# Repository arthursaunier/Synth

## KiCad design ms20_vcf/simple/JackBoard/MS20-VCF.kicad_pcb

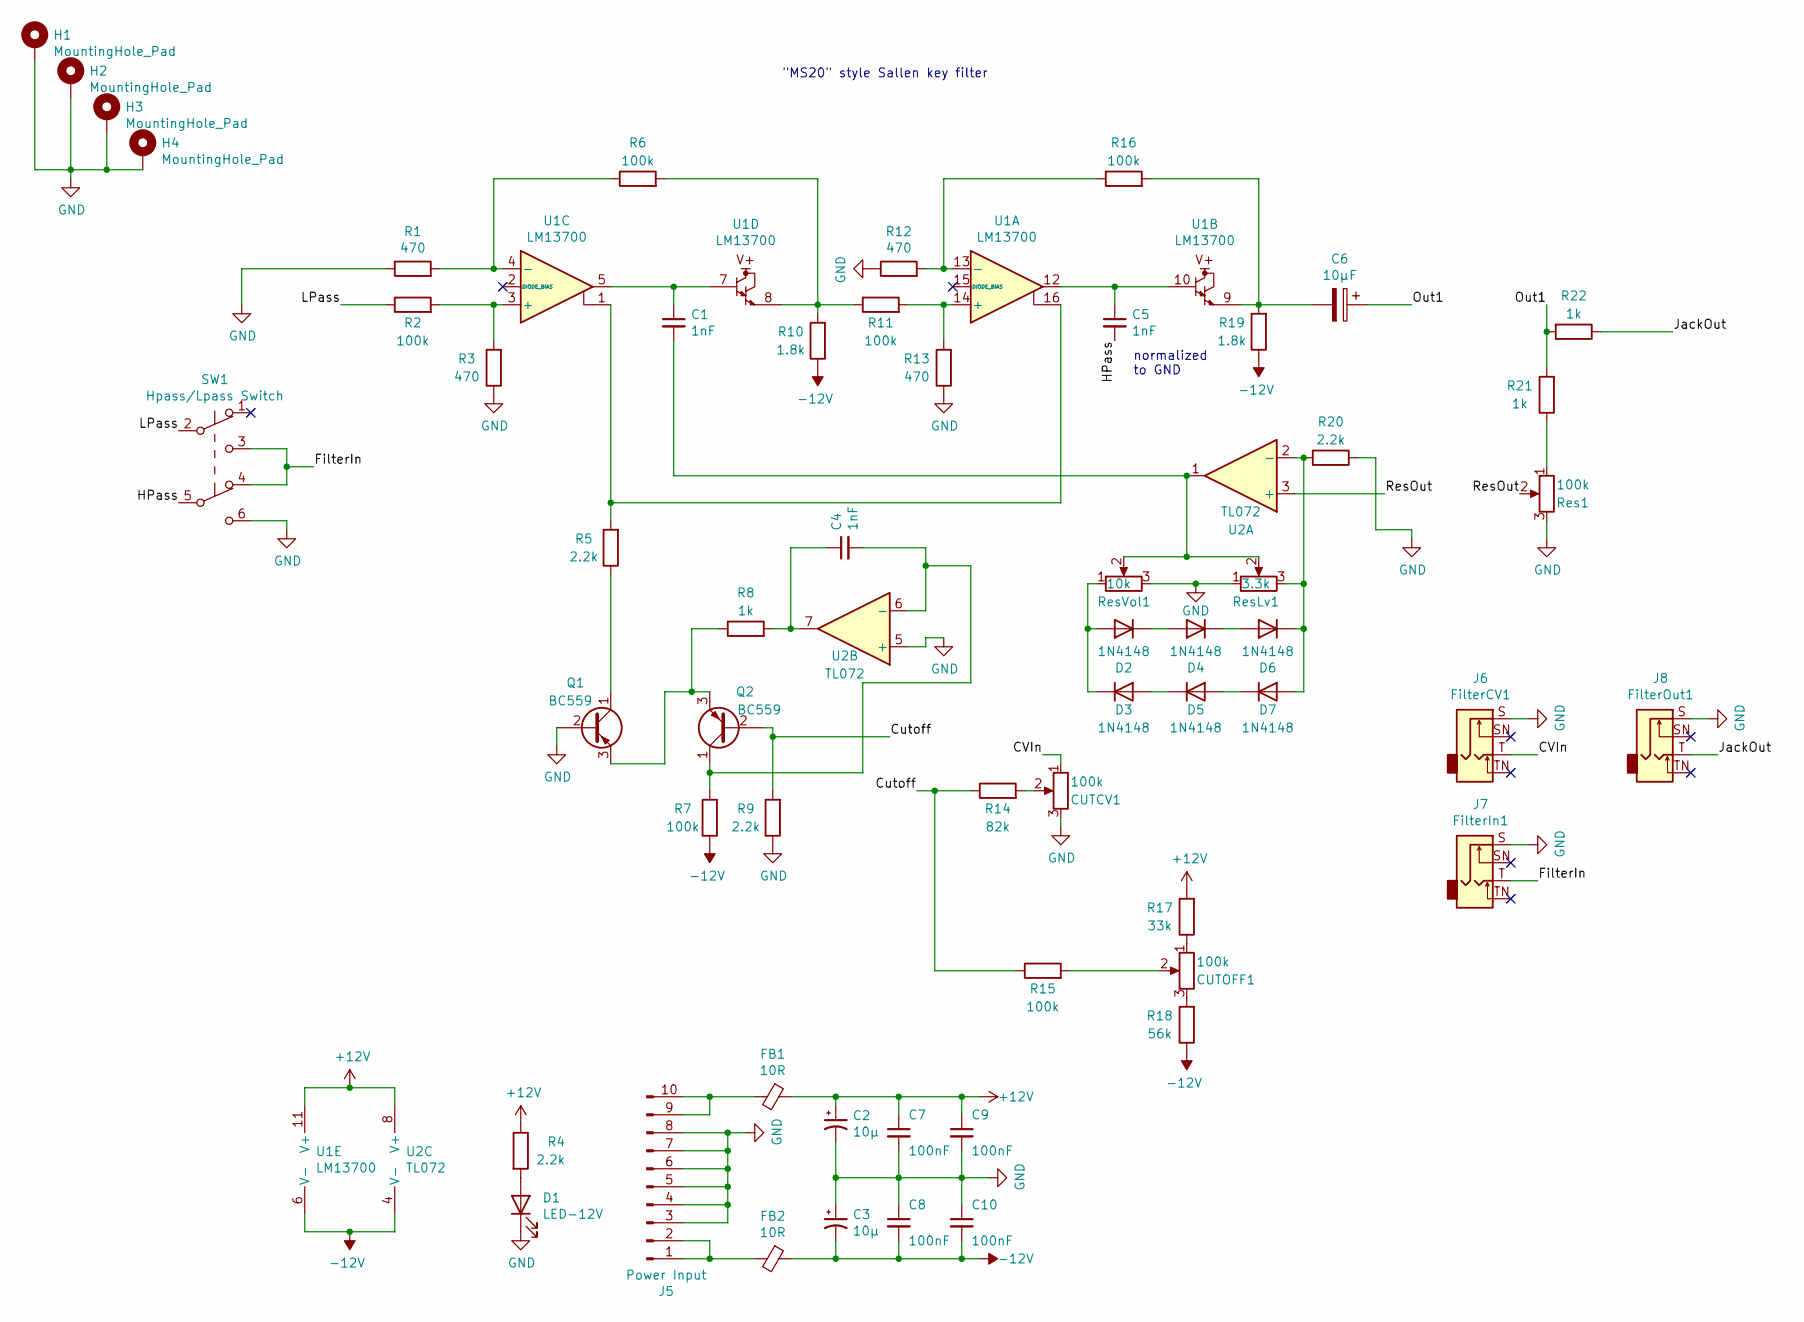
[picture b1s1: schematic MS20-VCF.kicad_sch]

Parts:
C1, C4, C5: 1nF; C_Disc_D7.0mm_W2.5mm_P5.00mm
C2, C3: 10µ; CP_Radial_D5.0mm_P2.00mm
C6: 10µF; CP_Radial_D5.0mm_P2.00mm
C7, C8, C9, C10: 100nF; C_Disc_D7.0mm_W2.5mm_P5.00mm
CUTCV1: 100k; Pot-bourns-alpha
CUTOFF1: 100k; Pot-bourns-alpha
D1: LED-12V; LED_D4.0mm
D2, D3, D4, D5, D6, D7: 1N4148; D_DO-35_SOD27_P7.62mm_Horizontal
FB1, FB2: 10R; L_Axial_L9.5mm_D4.0mm_P12.70mm_Horizontal_Fastron_SMCC
H1, H2, H3, H4: MountingHole_Pad; Doepfer Mounting hole
J5: Power Input; IDC-Header_2x05_P2.54mm_Vertical
J6: FilterCV1; Thonkiconn
J7: FilterIn1; Thonkiconn
J8: FilterOut1; Thonkiconn
Q1, Q2: BC559; TO-92_Inline_Wide
R1, R3, R12, R13: 470; R_Axial_DIN0207_L6.3mm_D2.5mm_P10.16mm_Horizontal
R2, R6, R7, R11, R15, R16: 100k; R_Axial_DIN0207_L6.3mm_D2.5mm_P10.16mm_Horizontal
R4, R5, R9, R20: 2.2k; R_Axial_DIN0207_L6.3mm_D2.5mm_P10.16mm_Horizontal
R8, R21, R22: 1k; R_Axial_DIN0207_L6.3mm_D2.5mm_P10.16mm_Horizontal
R10, R19: 1.8k; R_Axial_DIN0207_L6.3mm_D2.5mm_P10.16mm_Horizontal
R14: 82k; R_Axial_DIN0207_L6.3mm_D2.5mm_P10.16mm_Horizontal
R17: 33k; R_Axial_DIN0207_L6.3mm_D2.5mm_P10.16mm_Horizontal
R18: 56k; R_Axial_DIN0207_L6.3mm_D2.5mm_P10.16mm_Horizontal
Res1: 100k; Pot-bourns-alpha
ResLv1: 3.3k; Potentiometer_Bourns_3386C_Horizontal
ResVol1: 10k; Potentiometer_Bourns_3386C_Horizontal
SW1: Hpass/Lpass Switch; SW_DPDT_Toggle
U1: LM13700; SOIC-16_3.9x9.9mm_P1.27mm
U2: TL072; DIP-8_W7.62mm_Socket

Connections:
+12V: C2.1, C7.1, C9.1, FB1.1, R4.1, R17.2, U1.11 (V+), U2.8 (V+)
-12V: C3.2, C8.2, C10.2, FB2.1, R7.1, R10.1, R18.1, R19.1, U1.6 (V-), U2.4 (V-)
/CVIn: CUTCV1.1, J6.T
/Cutoff: Q2.2 (B), R9.2, R14.1, R15.1
/FilterIn: J7.T, SW1.3 (C), SW1.4 (A)
/HPass: C5.2, SW1.5 (B)
/JackOut: J8.T, R22.1
/LPass: R2.1, SW1.2 (B)
/Out1: C6.1, R21.2, R22.2
/ResOut: Res1.2, U2.3 (+)
GND: C2.2, C3.1, C7.2, C8.1, C9.2, C10.1, CUTCV1.3, D1.1 (K), H1.1, H2.1, H3.1, H4.1, J5.3, J5.4, J5.5, J5.6, J5.7, J5.8, J6.S, J7.S, J8.S, Q1.2 (B), R1.1, R3.1, R9.1, R12.1, R13.1, R20.1, Res1.3, ResLv1.1, ResVol1.3, SW1.6 (C), U2.5 (+)
unnamed: C1.1, U1.5, U1.7
unnamed: C1.2, ResLv1.2, ResVol1.2, U2.1
unnamed: C4.1, R8.2, U2.7
unnamed: C4.2, Q2.1 (C), R7.2, U2.6 (-)
unnamed: C5.1, U1.10, U1.12
unnamed: C6.2, R16.2, R19.2, U1.9
unnamed: CUTOFF1.1, R17.1
unnamed: D1.2 (A), R4.2
unnamed: D2.1 (K), D4.2 (A)
unnamed: D2.2 (A), D3.1 (K), ResVol1.1
unnamed: D3.2 (A), D5.1 (K)
unnamed: D4.1 (K), D6.2 (A)
unnamed: D5.2 (A), D7.1 (K)
unnamed: D6.1 (K), D7.2 (A), R20.2, ResLv1.3, U2.2 (-)
unnamed: FB1.2, J5.9, J5.10
unnamed: FB2.2, J5.1, J5.2
unnamed: Q1.1 (C), R5.1
unnamed: Q1.3 (E), Q2.3 (E), R8.1
unnamed: R1.2, R6.1, U1.4 (-)
unnamed: R2.2, R3.2, U1.3 (+)
unnamed: R5.2, U1.1, U1.16
unnamed: R6.2, R10.2, R11.1, U1.8
unnamed: R11.2, R13.2, U1.14 (+)
unnamed: R12.2, R16.1, U1.13 (-)
unnamed: CUTCV1.2, R14.2
unnamed: CUTOFF1.2, R15.2
unnamed: CUTOFF1.3, R18.2
unnamed: R21.1, Res1.1

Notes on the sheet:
normalized to GND
"MS20" style Sallen key filter

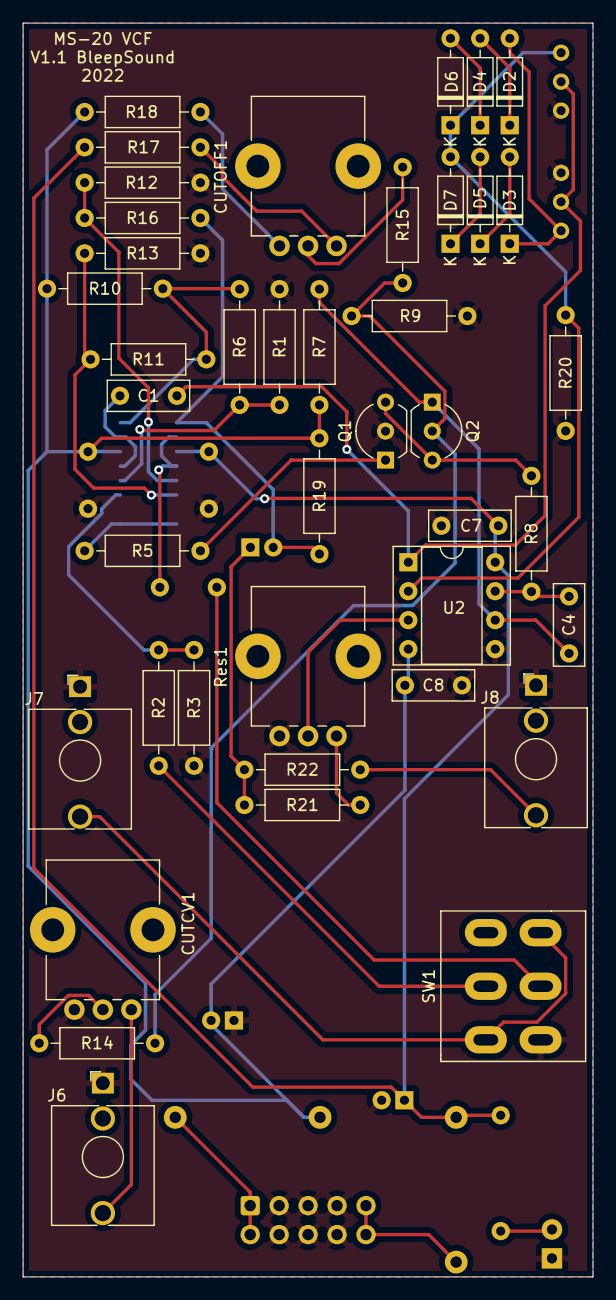
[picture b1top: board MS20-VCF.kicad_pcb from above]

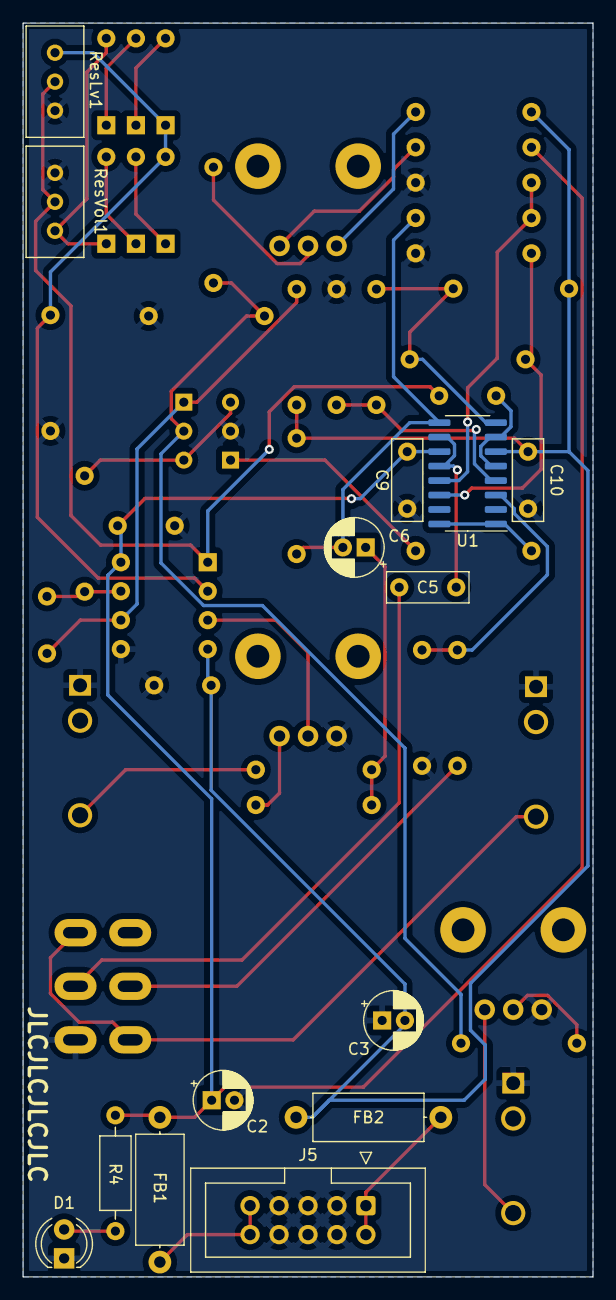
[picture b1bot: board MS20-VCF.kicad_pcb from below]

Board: 2 copper layers, 50.0 x 110.0 mm, 55 parts (14 on the bottom side), 39 nets.

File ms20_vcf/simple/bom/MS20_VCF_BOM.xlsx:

References | Quantity | Value | Footprint | Specs | Link | Price/100 | Price
C7, C8, C9, C10 | 4 | 100nF | C_Disc_D7.0mm_W2.5mm_P5.00mm | 100nF, 50V, ceramic disc | https://www.taydaelectronics.com/capacitors/ceramic-disc-cap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 | 0.01 | 0.04
C1, C4, C5 | 3 | 1nF | C_Disc_D7.0mm_W2.5mm_P5.00mm | 1nF, 50V, ceramic disc | https://www.taydaelectronics.com/capacitors/ceramic-disc-cap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 | 0.01 | 0.03
C2, C3, C6 | 3 | 10µ | CP_Radial_D5.0mm_P2.00mm | 10µF, 50V | https://www.taydaelectronics.com/capacitors/electrolytic-cap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 | 0.02 | 0.06
FB1, FB2 | 2 | 10R | L_Axial_L9.5mm_D4.0mm_P12.70mm_Horizontal_Fastron_SMCC |  | https://www.taydaelectronics.com/axial-ferrite-bead-76-ohm.html | 0.08 | 0.16
R2, R6, R7, R11, R15, R16 | 6 | 100k | R_Axial_DIN0207_L6.3mm_D2.5mm_P10.16mm_Horizontal | 1/4W metal film 1% resistor | https://www.taydaelectronics.com/resistors/1-4w-metal-film-r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 | 1.4999999999999999E-2 | 0.09
R1, R3, R12, R13 | 4 | 470R | R_Axial_DIN0207_L6.3mm_D2.5mm_P10.16mm_Horizontal | 1/4W metal film 1% resistor | https://www.taydaelectronics.com/resistors/1-4w-metal-film-r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 | 1.4999999999999999E-2 | 0.06
R4, R5, R9, R20 | 4 | 2.2k | R_Axial_DIN0207_L6.3mm_D2.5mm_P10.16mm_Horizontal | 1/4W metal film 1% resistor | https://www.taydaelectronics.com/resistors/1-4w-metal-film-r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 | 1.4999999999999999E-2 | 0.06
R8, R21, R22 | 3 | 1k | R_Axial_DIN0207_L6.3mm_D2.5mm_P10.16mm_Horizontal | 1/4W metal film 1% resistor | https://www.taydaelectronics.com/resistors/1-4w-metal-film-r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 | 1.4999999999999999E-2 | 4.4999999999999998E-2
R10, R19 | 2 | 1.8k | R_Axial_DIN0207_L6.3mm_D2.5mm_P10.16mm_Horizontal | 1/4W metal film 1% resistor | https://www.taydaelectronics.com/resistors/1-4w-metal-film-r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 | 1.4999999999999999E-2 | 0.03
R14 | 1 | 82k | R_Axial_DIN0207_L6.3mm_D2.5mm_P10.16mm_Horizontal | 1/4W metal film 1% resistor | https://www.taydaelectronics.com/resistors/1-4w-metal-film-r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 | 1.4999999999999999E-2 | 1.4999999999999999E-2
R17 | 1 | 33k | R_Axial_DIN0207_L6.3mm_D2.5mm_P10.16mm_Horizontal | 1/4W metal film 1% resistor | https://www.taydaelectronics.com/resistors/1-4w-metal-film-r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 | 1.4999999999999999E-2 | 1.4999999999999999E-2
R18 | 1 | 56k | R_Axial_DIN0207_L6.3mm_D2.5mm_P10.16mm_Horizontal | 1/4W metal film 1% resistor | https://www.taydaelectronics.com/resistors/1-4w-metal-film-r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 | 1.4999999999999999E-2 | 1.4999999999999999E-2
D2, D3, D4, D5, D6, D7 | 6 | 1N4148 | D_DO-35_SOD27_P7.62mm_Horizontal | 1N4148 diode | https://www.taydaelectronics.com/1n4148-switching-signal-diode.html | 0.01 | 0.06
D1 | 1 | LED-12V | LED_D4.0mm |  | https://www.taydaelectronics.com/leds/round-leds/5mm-leds.html | 0.03 | 0.03
U1 | 1 | LM13700 | SOIC-16_3.9x9.9mm_P1.27mm | OTA | https://www.taydaelectronics.com/lm13700-lm13700n-operationa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 | 3.99 | 1.99
U2 | 2 | TL072 | DIP-8_W7.62mm_Socket | OpAmp | https://www.taydaelectronics.com/tl072-low-noise-j-fet-dual-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 | 1.99 | 3.98
SW1 | 1 | Hpass/Lpass Switch | SW_DPDT_Toggle |  | https://www.taydaelectronics.com/mini-toggle-switch-dpdt-on-on.html | 0.59 | 0.59
CUTCV1, CUTOFF1, Res1 | 3 | 100k | Potentiometer_Bourns_PTV09A-1_Single_Vertical |  | https://www.mouser.fr/ProductDetail/652-PTV09A4025FB104 | 0.84699999999999998 | 2.5409999999999999
ResLv1 | 1 | 3.3k | Potentiometer_Bourns_3386C_Horizontal |  | https://www.taydaelectronics.com/10k-ohm-trimmer-potentiomet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 | 0.28000000000000003 | 0.28000000000000003
ResVol1 | 1 | 10k | Potentiometer_Bourns_3386C_Horizontal |  | https://www.taydaelectronics.com/10k-ohm-trimmer-potentiomet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 | 0.28000000000000003 | 0.28000000000000003
Q1, Q2 | 2 | BC559 | TO-92_Inline |  | https://www.taydaelectronics.com/bc559bta-bc559b-bc559-trans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 | 0.08 | 0.16
J5 | 1 | Power Input | IDC-Header_2x05_P2.54mm_Vertical |  | https://www.taydaelectronics.com/10-pin-box-header-connector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 | 0.15 | 0.15
J6, J7, J8 | 3 |  | Jack_3.5mm_QingPu_WQP-PJ398SM_Vertical_CircularHoles | 3,5mm mono Jack socket | https://www.thonk.co.uk/shop/3-5mm-jacks/ | 0.32 | 0.96
 |  |  |  |  |  | Total | 11.600999999999999

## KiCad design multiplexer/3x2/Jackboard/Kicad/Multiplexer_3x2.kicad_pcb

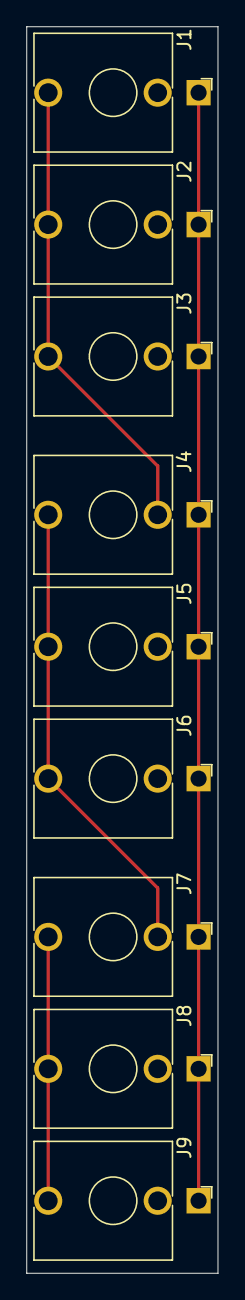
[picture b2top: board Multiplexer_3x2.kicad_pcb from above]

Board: 2 copper layers, 14.5 x 94.5 mm, 9 parts (0 on the bottom side), 4 nets.

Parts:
J1: In1; Jack_3.5mm_QingPu_WQP-PJ398SM_Vertical_CircularHoles
J2, J3: Out1; Jack_3.5mm_QingPu_WQP-PJ398SM_Vertical_CircularHoles
J4: In2; Jack_3.5mm_QingPu_WQP-PJ398SM_Vertical_CircularHoles
J5, J6: Out2; Jack_3.5mm_QingPu_WQP-PJ398SM_Vertical_CircularHoles
J7: In3; Jack_3.5mm_QingPu_WQP-PJ398SM_Vertical_CircularHoles
J8, J9: Out3; Jack_3.5mm_QingPu_WQP-PJ398SM_Vertical_CircularHoles

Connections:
GND: J1.S, J2.S, J3.S, J4.S, J5.S, J6.S, J7.S, J8.S, J9.S
unnamed: J4.T, J5.T, J6.T, J7.TN
unnamed: J1.T, J2.T, J3.T, J4.TN
unnamed: J7.T, J8.T, J9.T

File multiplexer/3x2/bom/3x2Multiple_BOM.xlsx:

References | Quantity | Value | Footprint | Specs | Link | Price/100 | Price
J1, J2, J3, J4, J5, J6, J7, J8, J9 | 9 | 4700µF | Jack_3.5mm_QingPu_WQP-PJ398SM_Vertical_CircularHoles | 3,5mm mono Jack socket | https://www.thonk.co.uk/shop/3-5mm-jacks/ | 0.28000000000000003 | 2.5200000000000005
- | 9 | - | - | Jack Hex nuts | https://www.thonk.co.uk/shop/3-5mm-jacks/ | 2.9000000000000001E-2 | 0.26100000000000001
- | 9 | - | - | Jack washers | https://www.thonk.co.uk/shop/3-5mm-jacks/ | 2.8000000000000001E-2 | 0.252
 |  |  |  |  |  | Total | 3.0330000000000004

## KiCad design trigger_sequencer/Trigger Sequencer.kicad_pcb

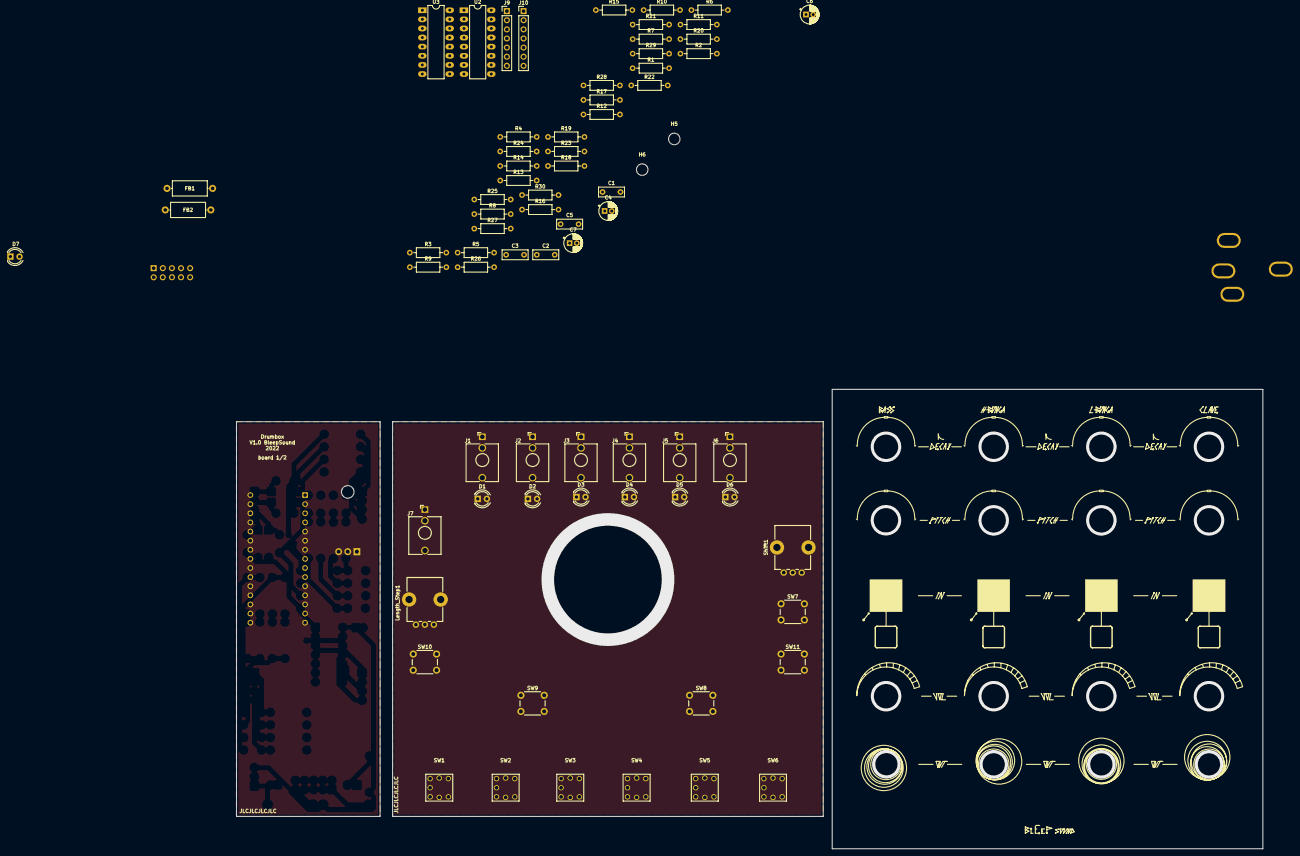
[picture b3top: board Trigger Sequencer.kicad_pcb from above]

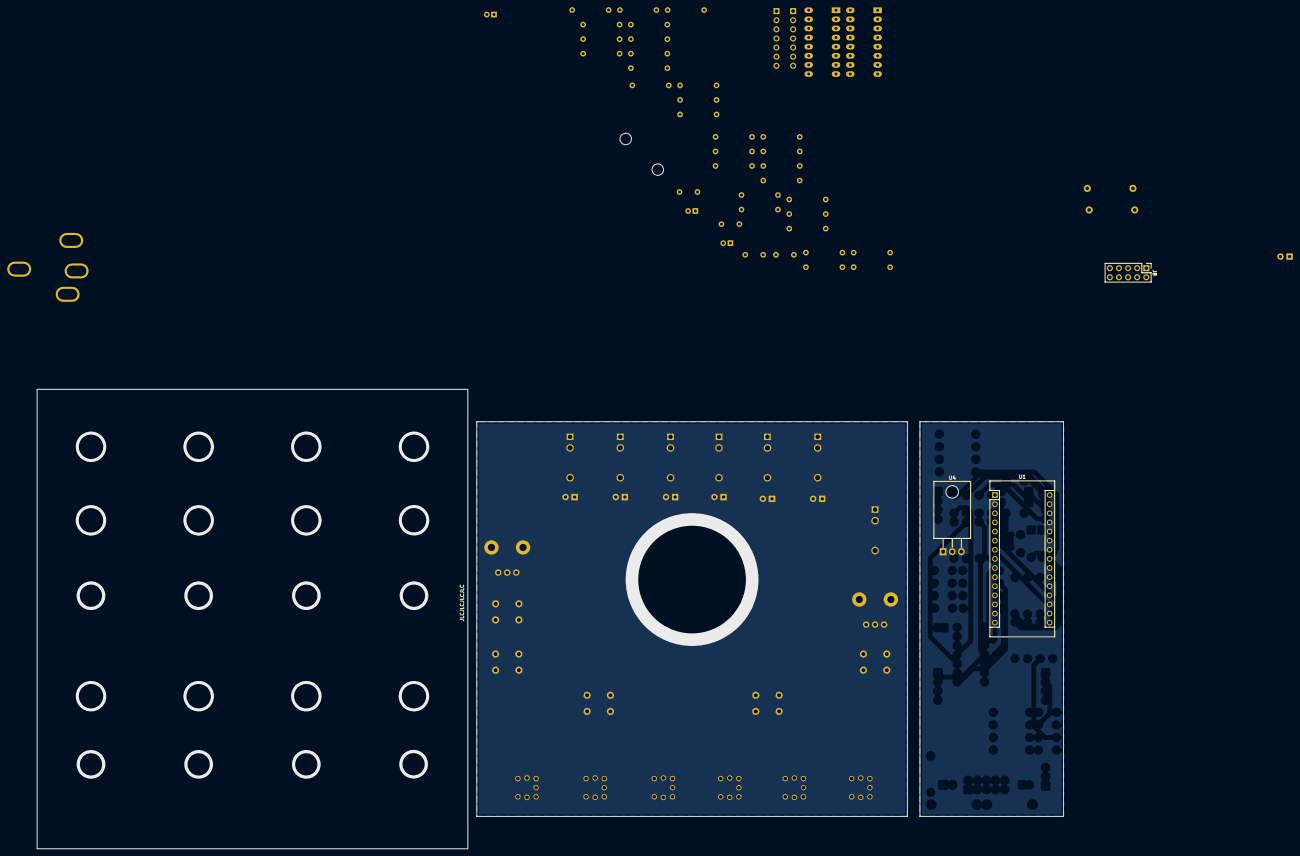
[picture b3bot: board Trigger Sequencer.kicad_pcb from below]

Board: 2 copper layers, 286.0 x 128.0 mm, 79 parts (3 on the bottom side), 58 nets, no tracks yet.

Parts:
C1, C2, C3, C5: 100nF; C_Disc_D7.0mm_W2.5mm_P5.00mm
C4, C6, C7: 10µ; CP_Radial_D5.0mm_P2.00mm
D1, D2, D3, D4, D5, D6: LED; LED_D4.0mm
D7: LED-12V; LED_D4.0mm
FB1, FB2: 10R; L_Axial_L9.5mm_D4.0mm_P12.70mm_Horizontal_Fastron_SMCC
H1, H2, H3, H4: MountingHole; Doepfer Mounting hole
H5, H6: SpacerHoles; MountingHole_3.2mm_M3
J1, J2, J3, J4, J5, J6: Out; Jack_3.5mm_QingPu_WQP-PJ398SM_Vertical_CircularHoles
J7: Clock-In; Jack_3.5mm_QingPu_WQP-PJ398SM_Vertical_CircularHoles
J8: Power Input; PinHeader_2x05_P2.54mm_Vertical
J9, J10: Conn_01x07_Male; PinHeader_1x07_P2.54mm_Vertical
Length_Step1: 10k; Potentiometer_Bourns_PTV09A-1_Single_Vertical
R1, R2, R3, R4, R5: 2k; R_Axial_DIN0207_L6.3mm_D2.5mm_P10.16mm_Horizontal
R6, R7, R8, R9, R10, R11, R12, R13, R14, R15, R16, R17: 1k; R_Axial_DIN0207_L6.3mm_D2.5mm_P10.16mm_Horizontal
R18, R20, R21, R22, R23, R24, R25, R26, R27, R28, R29, R30: 10k; R_Axial_DIN0207_L6.3mm_D2.5mm_P10.16mm_Horizontal
R19: 2.2k; R_Axial_DIN0207_L6.3mm_D2.5mm_P10.16mm_Horizontal
SW1, SW2, SW3, SW4, SW5, SW6: SW_MEC_LOW_PROF_LED; PB01-109TL
SW7, SW8, SW9, SW10, SW11: SW_MEC_5G; SW_PUSH_6mm_H13mm
Shift1: 10k; Potentiometer_Bourns_PTV09A-1_Single_Vertical
U1: Arduino_Nano_v3.x; Arduino_Nano
U2, U3: 74HCT4051; DIP-16_W7.62mm_LongPads
U4: L7805; TO-220-3_Horizontal_TabDown

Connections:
+5V: C1.1, C2.1, C3.1, C5.1, J9.1, J10.1, Length_Step1.1, R1.1, SW1.1, SW1.2, SW2.1, SW2.2, SW3.1, SW3.2, SW4.1, SW4.2, SW5.1, SW5.2, SW6.1, SW6.2, SW7.1 (A), SW7.2 (A), SW8.1 (A), SW8.2 (A), SW9.1 (A), SW9.2 (A), SW10.1 (A), SW10.2 (A), SW11.1 (A), SW11.2 (A), Shift1.1, U1.30 (VIN), U2.16 (VCC), U3.16 (VCC), U4.3 (OUT)
+12V: C4.1, C6.1, FB1.1, R19.1, U4.1 (IN)
-12V: C7.2, FB2.1
/Bank_Select: R24.2, U2.1 (A4)
/Channel select: J9.7, U1.19 (A0)
/Clear: R23.2, U2.12 (A3)
/Clock_In: J7.T, R18.1, U1.1 (D1/TX)
/Delete: R20.2, U2.13 (A0)
/Fill: R22.2, U2.15 (A2)
/Length: Length_Step1.2, U1.20 (A1)
/Out1: J1.T, R13.2, U1.11 (D8)
/Out2: J2.T, R14.2, U1.12 (D9)
/Out3: J3.T, R16.2, U1.13 (D10)
/Out4: J4.T, R12.2, U1.14 (D11)
/Out5: J5.T, R15.2, U1.15 (D12)
/Out6: J6.T, R17.2, U1.16 (D13)
/Reset: R21.2, U2.14 (A1)
/Shift: Shift1.2, U1.21 (A2)
/Trig1: R25.2, SW1.3, SW1.4, U3.13 (A0)
/Trig2: R26.2, SW2.3, SW2.4, U3.14 (A1)
/Trig3: R27.2, SW3.3, SW3.4, U3.15 (A2)
/Trig4: R28.2, SW4.3, SW4.4, U3.12 (A3)
/Trig5: R29.2, SW5.3, SW5.4, U3.1 (A4)
/Trig6: R30.2, SW6.3, SW6.4, U3.5 (A5)
/Trig_In: U1.5 (D2), U3.3 (A)
/Util_In: U1.6 (D3), U2.3 (A)
GND: C1.2, C2.2, C3.2, C4.2, C5.2, C6.2, C7.1, D1.1 (K), D2.1 (K), D3.1 (K), D4.1 (K), D5.1 (K), D6.1 (K), D7.1 (K), J1.S, J2.S, J3.S, J4.S, J5.S, J6.S, J7.S, J8.3, J8.4, J8.5, J8.6, J8.7, J8.8, J9.6, Length_Step1.3, R5.2, R18.2, R20.1, R21.1, R22.1, R23.1, R24.1, R25.1, R26.1, R27.1, R28.1, R29.1, R30.1, SW1.L2, SW2.L2, SW3.L2, SW4.L2, SW5.L2, SW6.L2, Shift1.3, U1.4 (GND), U1.29 (GND), U2.6 (~E), U2.7 (VEE), U2.8 (GND), U3.6 (~E), U3.7 (VEE), U3.8 (GND), U4.2 (GND)
unnamed: D1.2 (A), R6.1
unnamed: D2.2 (A), R7.1
unnamed: D3.2 (A), R8.1
unnamed: D4.2 (A), R9.1
unnamed: D5.2 (A), R10.1
unnamed: D6.2 (A), R11.1
unnamed: D7.2 (A), R19.2
unnamed: FB1.2, J8.1, J8.2
unnamed: FB2.2, J8.9, J8.10
unnamed: J9.2, R1.2, R2.1
unnamed: J9.3, R2.2, R3.1
unnamed: J9.4, R3.2, R4.1
unnamed: J9.5, R4.2, R5.1
unnamed: J10.2, R6.2
unnamed: J10.3, R7.2
unnamed: J10.4, R8.2
unnamed: J10.5, R9.2
unnamed: J10.6, R10.2
unnamed: J10.7, R11.2
unnamed: R12.1, SW4.L1
unnamed: R13.1, SW1.L1
unnamed: R14.1, SW2.L1
unnamed: R15.1, SW5.L1
unnamed: R16.1, SW3.L1
unnamed: R17.1, SW6.L1
unnamed: U1.8 (D5), U2.9 (S2)
unnamed: U1.9 (D6), U2.10 (S1)
unnamed: U1.10 (D7), U2.11 (S0)
unnamed: U1.22 (A3), U3.11 (S0)
unnamed: U1.23 (A4), U3.10 (S1)
unnamed: U1.24 (A5), U3.9 (S2)
